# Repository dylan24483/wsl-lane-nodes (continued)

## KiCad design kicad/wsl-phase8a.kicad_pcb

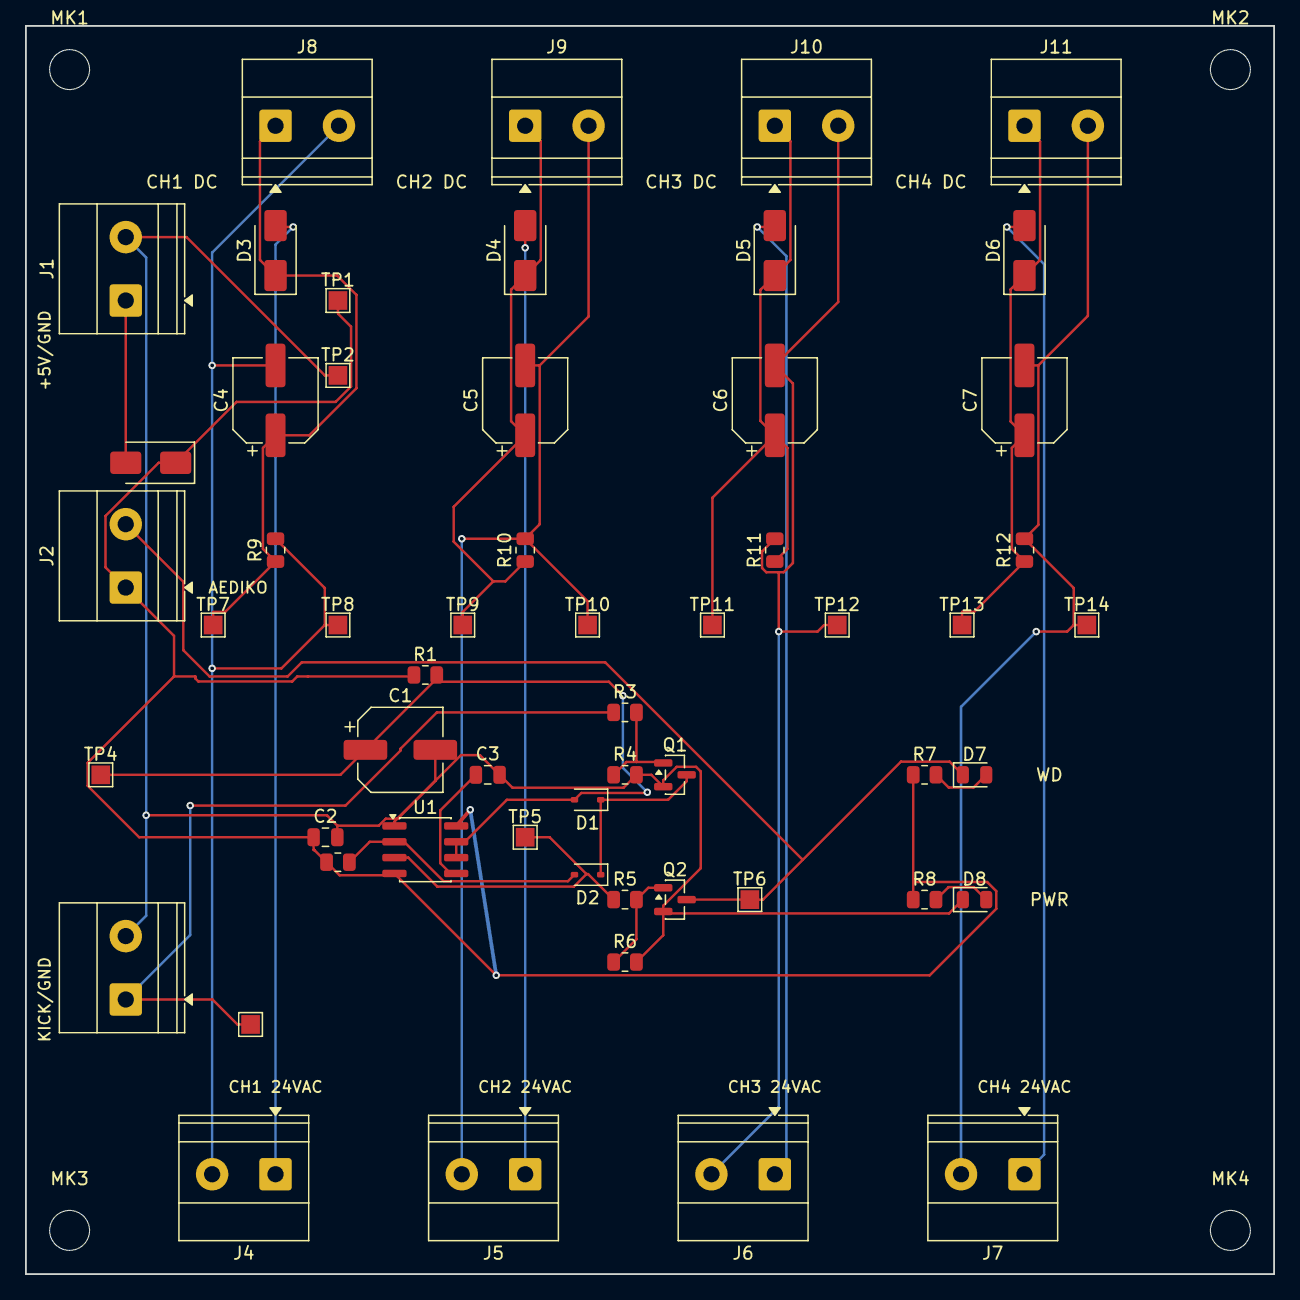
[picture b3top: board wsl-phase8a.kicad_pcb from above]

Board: 2 copper layers, 100.0 x 100.0 mm, 60 parts (0 on the bottom side), 26 nets.

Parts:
C1: 100uF/16V; CP_Elec_6.3x5.4
C2: 0.1uF/50V; C_0805_2012Metric
C3: 10nF/50V; C_0805_2012Metric
C4, C5, C6, C7: 10uF/63V; CP_Elec_6.3x5.4
D1, D2: 1N4148WS; D_SOD-323
D3, D4, D5, D6: M7 (1N4007); D_SMA
D7, D8: Green; LED_0805_2012Metric
D9: SS14; D_SMA
J1, J2, J3, J4, J5, J6, J7, J8, J9, J10, J11: 5.08mm 2P TB; TerminalBlock_Phoenix_MKDS-1,5-2-5.08_1x02_P5.08mm_Horizont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
MK1, MK2, MK3, MK4: MountingHole_3.2mm_M3
Q1, Q2: AO3400A; SOT-23
R1, R9, R10, R11, R12: 100k; R_0805_2012Metric
R2, R4, R6: 10k; R_0805_2012Metric
R3, R5: 1k; R_0805_2012Metric
R7, R8: 470; R_0805_2012Metric
TP1: VCC_5V; TestPoint_Pad_1.5x1.5mm
TP2: GND; TestPoint_Pad_1.5x1.5mm
TP3: KICK; TestPoint_Pad_1.5x1.5mm
TP4: TIMING_NODE; TestPoint_Pad_1.5x1.5mm
TP5: NE555_OUT; TestPoint_Pad_1.5x1.5mm
TP6: COIL_GND_RETURN; TestPoint_Pad_1.5x1.5mm
TP7: DC_CH1_POS; TestPoint_Pad_1.5x1.5mm
TP8: CH1_RETURN; TestPoint_Pad_1.5x1.5mm
TP9: DC_CH2_POS; TestPoint_Pad_1.5x1.5mm
TP10: CH2_RETURN; TestPoint_Pad_1.5x1.5mm
TP11: DC_CH3_POS; TestPoint_Pad_1.5x1.5mm
TP12: CH3_RETURN; TestPoint_Pad_1.5x1.5mm
TP13: DC_CH4_POS; TestPoint_Pad_1.5x1.5mm
TP14: CH4_RETURN; TestPoint_Pad_1.5x1.5mm
U1: NE555; SOIC-8_3.9x4.9mm_P1.27mm

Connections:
AC_CH1_L1: D3.2, J4.1
AC_CH2_L1: D4.2, J5.1
AC_CH3_L1: D5.2, J6.1
AC_CH4_L1: D6.2, J7.1
CH1_RETURN: C4.2, J4.2, J8.2, R9.2, TP8.1
CH2_RETURN: C5.2, J5.2, J9.2, R10.2, TP10.1
CH3_RETURN: C6.2, J6.2, J10.2, R11.2, TP12.1
CH4_RETURN: C7.2, J7.2, J11.2, R12.2, TP14.1
COIL_GND_RETURN: D7.1, J2.2, Q2.3, TP6.1
DC_CH1_POS: C4.1, D3.1, J8.1, R9.1, TP7.1
DC_CH2_POS: C5.1, D4.1, J9.1, R10.1, TP9.1
DC_CH3_POS: C6.1, D5.1, J10.1, R11.1, TP11.1
DC_CH4_POS: C7.1, D6.1, J11.1, R12.1, TP13.1
GND: C1.2, C2.2, C3.2, D8.1, J1.2, J3.2, Q1.2, Q2.2, R4.2, R6.2, TP2.1, U1.1
KICK: J3.1, R3.1, TP3.1
LED1_ANODE_DRIVE: D7.2, R7.2
LED2_ANODE_DRIVE: D8.2, R8.2
NE555_CTRL: C3.1, U1.5
NE555_OUT: R5.1, TP5.1, U1.3
NE555_TRIG: D2.2, R2.2, U1.2
Q1_DRAIN: D1.1, D2.1, Q1.3
Q1_GATE: Q1.1, R3.2, R4.1
Q2_GATE: Q2.1, R5.2, R6.1
TIMING_NODE: C1.1, D1.2, R1.2, TP4.1, U1.6, U1.7
VCC_5V: C2.1, D9.1, J2.1, R1.1, R2.1, R7.1, R8.1, TP1.1, U1.4, U1.8
VCC_5V_RAW: D9.2, J1.1

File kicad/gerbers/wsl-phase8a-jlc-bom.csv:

"Comment","Designator","Footprint","LCSC Part #"
"100uF/16V","C1","CP_Elec_6.3x5.4","C970684"
"0.1uF/50V","C2","C_0805_2012Metric","C49678"
"10nF/50V","C3","C_0805_2012Metric","C53084521"
"10uF/63V","C4,C5,C6,C7","CP_Elec_6.3x5.4","C2935114"
"1N4148WS","D1,D2","D_SOD-323","C917117"
"M7 (1N4007)","D3,D4,D5,D6","D_SMA","C95872"
"Green","D7,D8","LED_0805_2012Metric","C84260"
"SS14","D9","D_SMA","C2480"
"AO3400A","Q1,Q2","SOT-23","C20917"
"100k","R1,R9,R10,R11,R12","R_0805_2012Metric","C149504"
"10k","R2,R4,R6","R_0805_2012Metric","C2930231"
"1k","R3,R5","R_0805_2012Metric","C2907295"
"470","R7,R8","R_0805_2012Metric","C2907329"
"NE555","U1","SOIC-8_3.9x4.9mm_P1.27mm","C7593"

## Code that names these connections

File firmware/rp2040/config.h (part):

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
/* ---- UART (uart0) link to the Pi -------------------------------------------------------- */
#define UART_BAUD     115200
#define PIN_UART_TX   0   /* GP0, Pico pin 1  -> Pi RX   (net PI_UART_RX) */
#define PIN_UART_RX   1   /* GP1, Pico pin 2  <- Pi TX   (net PI_UART_TX) */

/* ---- Rail permission output ------------------------------------------------------------- */
#define PIN_RP_OK     2   /* GP2, Pico pin 4  -> RP2040_OK; HIGH=permit motion, LOW=drop rail */

/* ---- Fast inputs (opto, ACTIVE-LOW: asserted = GPIO LOW) -------------------------------- */
#define PIN_SA        6   /* GP6,  Pico pin 9  : sweep cam  (270 run-through stop / 360 zero)  */
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 * registers each heartbeat tick and latch_fault()s (fail-safe: drops RP_OK) on any
 * drift. The host test (test/test_v12.c) fails the build if any code path ever puts
 * GP16-19 in an output direction or writes them.                                        */
#define PIN_TAP_555    16   /* GP16, Pico pin 21 : TAP_NE555_OUT   (INVERTED: raw 0 = 555 out HIGH) */
#define PIN_TAP_KICK   17   /* GP17, Pico pin 22 : TAP_WDOG_KICK   (INVERTED)                       */
#define PIN_TAP_ARM    18   /* GP18, Pico pin 24 : TAP_ARM_PERMIT  (INVERTED)                       */
#define PIN_TAP_RPOK   19   /* GP19, Pico pin 25 : TAP_RP2040_OK   (INVERTED; cross-checked vs GP2) */
#define PIN_ADC_VCC5   26   /* GP26/ADC0, Pico pin 31 : ADC_VCC5_SENSE = VCC_5V/2 (10k/10k divider) */
#define ADC_VCC5_INPUT  0   /* ADC mux input for GP26 */

/* ---- v1.2.2 REV_ID board-revision straps (Codex R2-6) ----------------------------------- */
/* AUTHORITATIVE SOURCE: generate_kicad_netlist_revD.py block_j16_protection_and_revid()
 * (committed 2026-07-21, dc56964). GP20 (Pico pin 26) = REV_ID0, 10k strap; GP21 (Pico
 * pin 27) = REV_ID1, 10k strap. ENCODING: REV_ID[1:0] = GP21<<1 | GP20.
 *   rev-D board: REV_ID0 strapped to VCC_3V3 (reads 1), REV_ID1 to GND (reads 0) = 0b01.
 *   0b00 = reserved/legacy; 0b10/0b11 = future revisions.
 * On a rev-B/rev-C board these pins are UNCONNECTED (float). Detection: read once under
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 * reads = floating = REV_ID_FLOATING (reported "unknown", NEVER assumed rev-D). After the
 * read, pulls are disabled (zero static strap current) and the pins join the pad-OE
 * locked input-contract set.                                                              */
#define PIN_REV_ID0      20   /* GP20, Pico pin 26 : REV_ID bit 0 (rev-D: 10k to VCC_3V3) */
#define PIN_REV_ID1      21   /* GP21, Pico pin 27 : REV_ID bit 1 (rev-D: 10k to GND)     */
#define REV_ID_REVD      0x1u /* the code THIS firmware expects on a rev-D board          */
#define REV_ID_FLOATING  0xFFu/* sentinel: pull-phase reads disagreed (no straps fitted)  */
#define REV_ID_SETTLE_US 50u  /* pull -> read settle (10k/50k node settles in ~us; ample) */
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
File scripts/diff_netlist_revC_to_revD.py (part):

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# docs/phase8_revD_change_spec.md items A/C/D/E/F:
ALLOWED_TOUCHED_NETS = {
    "FIELD_WET_V",    # A: bleed pair; C: 8 x Rin_AUXn
    "FIELD_GND",      # A: bleed pair; C: J15 pins 9-10
    "VCC_5V",         # D: divider top; R2-4: F_J16_5V polyfuse input
                      #   (J16 pin 1 moved behind it, 2026-07-21 round 2)
    "GND",            # C: 8 x opto emitter; D: divider bottom + cap;
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                      # R2-4: buffer GND + bypass + ESD VN/spare; R2-6: REV_ID1 strap
    "VCC_3V3",        # C: 8 x Rpu_AUXn; E(R1): 4 x R_TAPPU; R2-4: solder-link
                      #   input + buffer VCC/EN + card-side pull-ups + bypass
                      #   (J16 pin 5 moved behind the link); R2-6: REV_ID0 strap
    "I2C_SDA",        # R2-4: TCA4307 SDAIN (J16 pin 3 moved behind the buffer)
    "I2C_SCL",        # R2-4: TCA4307 SCLIN (J16 pin 4 moved behind the buffer)
    "NE555_OUT",      # E(R1): R_TAPIN_555 series input
    "WDOG_KICK",      # E(R1): R_TAPIN_KICK series input
    "ARM_PERMIT",     # E(R1): R_TAPIN_ARM series input
    "RP2040_OK",      # E(R1): R_TAPIN_RPOK series input
}

# --------------------------------------------------------------------------
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                  ("R_WET_BLEED1", "2"), ("R_WET_BLEED2", "2")},
    "FIELD_WET_V": ({("R_WET_BLEED1", "1"), ("R_WET_BLEED2", "1")}
                    | {(f"Rin_AUX{i}", "1") for i in range(4, 12)}),
    # R2-4 (2026-07-21): J16 pin 1 now lands on J16_5V (an ADDED net).
    # Round-3: ESD VP (D_ESD_J16.5) rides VCC_5V UPSTREAM of the polyfuse.
    "VCC_5V": {("F_J16_5V", "1"), ("R_ADC5_TOP", "1"), ("D_ESD_J16", "5")},
    "GND": ({("C_ADC5", "2"), ("J_EXTI2C", "2"), ("J_EXTI2C", "6"),
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                | {("JP_J16_3V3", "1"), ("U_I2C_BUF", "8"), ("U_I2C_BUF", "1"),
                   ("R_J16_SDA_PU", "1"), ("R_J16_SCL_PU", "1"),
                   ("C_I2C_BUF", "1"), ("R_REVID0", "1")}),
    "I2C_SDA": {("U_I2C_BUF", "6")},   # R2-4: SDAIN (J16 pin 3 now buffered)
    "I2C_SCL": {("U_I2C_BUF", "3")},   # R2-4: SCLIN (J16 pin 4 now buffered)
    "NE555_OUT": {("R_TAPIN_555", "1")},
    "WDOG_KICK": {("R_TAPIN_KICK", "1")},
    "ARM_PERMIT": {("R_TAPIN_ARM", "1")},
    "RP2040_OK": {("R_TAPIN_RPOK", "1")},
}
for _n in R6_REVC_CHANNELS:                                            # r6
    EXPECTED_TOUCHED_NET_ADDITIONS[f"FIELD_LED_{_n}"] = {
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
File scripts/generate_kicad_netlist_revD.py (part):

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  C - IN-B GPB opto bank: 8 exact opto_input() clones AUX4-AUX11 appended at
      the END of SLOW_INPUT_PINS -> MCP_IN_B (0x21) pins 1-8 (GPB0-7), plus
      new field connector J15 = J_SLOW_IN_C (Conn_01x10 on FP_MCV_1X10,
      pinout mirrors J3 keying: signals 1-8, FIELD_GND 9-10). Mating plug
      Phoenix MC 1,5/10-ST-3,5 = 1840447 (harness BOM) — SAME plug PN as J3
      on the same field edge: cross-mate hazard; CP-MSTB 1734634 coding keys
      at different positions are MANDATORY (spec §C.3, gate OG-3).
      25 parts, 24 new nets.
  D - VCC_5V board-self-health ADC divider: 10k/10k + 100nF -> new net
      ADC_VCC5_SENSE -> Pico pin 31 (GP26/ADC0). ADC_VREF (pin 35) stays NC
      (module-internal reference, spec drift DR-3). 3 parts, 1 new net.
  E - Rail-drop edge-ordering taps on EXISTING observable points only.
      2026-07-21 REDESIGN (remediation spec R1, closes Codex C1 + H1 —
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INT_B = Net("MCP_INT_B")
RAIL_EN = Net("RELAY_ENABLE_RAIL")
# Rev-D round-2 (Codex R2-4): J16 no longer touches the raw rails/bus.
# Pin 1 sits behind a 200 mA polyfuse (J16_5V), pin 5 behind a default-OPEN
# solder link (J16_3V3), pins 3/4 behind a TCA4307 stuck-bus-recovery I2C
# buffer (J16_SDA/J16_SCL). All four are LOGIC-domain nets.
J16_5V = Net("J16_5V")
J16_3V3 = Net("J16_3V3")
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    led_series = Net(f"FIELD_LED_{name}")

    # Dry-contact default: WET -> Rin -> Dser -> opto LED -> field pin. The
    # field contact closes that pin to FIELD_GND at the connector/harness.
    WET += rin[1]
    rin_series += rin[2]
    led_series += opto[1]
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    FGND += j_slowb[12]

    # Rev-D item C: J15 pinout mirrors J3's keying pattern (signals 1-8,
    # doubled FIELD_GND on the last two pins).
    slowc_order = [f"AUX{i}" for i in range(4, 12)]
    for pin, name in enumerate(slowc_order, start=1):
        slow_field[name] += j_slowc[pin]
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    # Rev-D item F, REVISED by round-2 remediation R2-4 (2026-07-21): the
    # J16 pin functions are unchanged (5V / GND / SDA / SCL / 3V3 / GND) but
    # every non-GND pin now lands on a PROTECTED net:
    #   pin 1 -> J16_5V   (behind the F_J16_5V 200 mA polyfuse)
    #   pin 3 -> J16_SDA  (behind the TCA4307 buffer + local pull-up + ESD)
    #   pin 4 -> J16_SCL  (ditto)
    #   pin 5 -> J16_3V3  (behind the JP_J16_3V3 default-OPEN solder link —
    #                      the pin ships NC; bridge only for a verified
    #                      3.3 V module)
    # A wedged/shorted external module can no longer wedge the main I2C bus
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    polyfuse are NOT isolation-barrier parts — every pin lands on LOGIC
    nets; the PC817/G5LE barrier inventory is untouched):
      * F_J16_5V  — Littelfuse 1206L020YR polyfuse (200 mA hold / 420 mA
        trip / 24 V @ 23 C), VCC_5V -> J16_5V -> J16 pin 1. Protects the
        module branch; PPTC trip current is time/temperature dependent, not
        a hard current clamp. The
        sanctioned steady module allowance is 45 mA (R3-7, re-derived from
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        the polyfuse (round-3 fix — VP on the fused J16_5V node let a
        bridged-JP1 board defeat the fuse through IO1's upper steering
        diode on a J16 5V-to-GND short), steering IOs on J16_SDA (3),
        J16_SCL (6), J16_3V3 (1), and J16_5V (4) so the fused 5 V pin
        keeps its ESD clamp.

    REV_ID straps (Codex R2-6): 2-bit board-revision code on spare Pico
    GPIOs, read by firmware (v1.2.2 task) and reported in the identity
    line so the daemon can reject roles unsupported by the physical board.
      * GP20 (pin 26) = REV_ID0 — 10k strap to VCC_3V3 (reads 1)
      * GP21 (pin 27) = REV_ID1 — 10k strap to GND     (reads 0)
    ENCODING (REV_ID[1:0] = GP21<<1 | GP20):
      0b00 = reserved/legacy (no straps — a rev-C-class board would float;
             firmware must treat unreadable/floating as UNKNOWN, not rev-D)
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    #     J16_5V node permanently). Now: VP rides VCC_5V UPSTREAM of the
    #     polyfuse (a solid rail — steering diodes from any shorted IO pin
    #     are reverse-biased, clamp energy still lands on a decoupled rail)
    #     and the fused J16_5V pin gets the previously-spare IO3 channel so
    #     the connector's 5 V pin keeps ESD protection. Under the same
    #     fault: IO3 lower diode to VN reverse-biased, IO3 upper diode
    #     (0 V -> 5 V VP) reverse-biased — NO sneak path, fuse does its job. ---
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    J16_3V3 += esd[1]            # IO1
    GND += esd[2]                # VN
    J16_SDA += esd[3]            # IO2
    J16_5V += esd[4]             # IO3 — fused 5V pin as an IO channel (round-3)
    VCC5 += esd[5]               # VP — UPSTREAM of the polyfuse (round-3)
    J16_SCL += esd[6]            # IO4

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    r_id1 = add_res("R_REVID1", "10k")
    rev0 = Net("REV_ID0")
    rev1 = Net("REV_ID1")
    VCC3V3 += r_id0[1]           # rev-D: REV_ID0 = 1
    rev0 += r_id0[2], pico[26]   # GP20
    GND += r_id1[1]              # rev-D: REV_ID1 = 0
    rev1 += r_id1[2], pico[27]   # GP21


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
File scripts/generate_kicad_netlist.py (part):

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  LED1, LED2     LED1, LED2    Watchdog-healthy + power-good indicators
  TB_PWR_IN      J1            +5V power input
  TB_AEDIKO_PWR  J2            5V out to AEDIKO PWR (V+ direct, V- gated by Q2)
  TB_KICK        J3            Pi GPIO 12 watchdog kick input
  TB_AC_IN_CH*   J4..J7        24VAC channel inputs (foul/2nd-ball lamps)
  TB_DC_OUT_CH*  J8..J11       DC channel outputs to AL-ZARD selector inputs

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GND += LED2['K']  # LED2 cathode (power-good LED, cathode to GND)
GND += J3[2]      # TB_KICK.2 (kick GND reference, back to Pi)

# --- KICK (Pi GPIO 12 input to watchdog) ---
KICK += J3[1]     # TB_KICK.1
KICK += R3[1]     # Q1 gate series, top

# --- Q1_GATE (gate-drive network) ---
Q1_GATE += R3[2]  # Q1 gate series, bottom
Q1_GATE += R4[1]  # Q1 gate pulldown, top
Q1_GATE += Q1[1]  # Q1 gate (SOT-23 pin 1 = G)

# --- Q1_DRAIN (diode-OR isolation node) ---
Q1_DRAIN += Q1[3]    # Q1 drain (SOT-23 pin 3 = D)
Q1_DRAIN += D1['K']  # D1 cathode (Q1 pulls this LOW when ON)
Q1_DRAIN += D2['K']  # D2 cathode

# --- TIMING_NODE (NE555 RC + diode-OR anode for TIMING) ---
TIMING_NODE += U1[6]    # THRES (NE555 pin 6)
TIMING_NODE += U1[7]    # DISCH (NE555 pin 7)
TIMING_NODE += R1[2]    # Timing pullup, bottom
TIMING_NODE += C1[1]  # Timing cap +
TIMING_NODE += D1['A']  # D1 anode — when Q1 ON, D1 pulls TIMING_NODE down
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
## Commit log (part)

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2026-05-02 Initial commit: night-1 Phase 8 prototype with real wsl_scoring_engine
2026-05-02 Add server-initiated commands (OPEN/CLOSE/RESET) + desk simulator UI
    - Pi handles new command types with distinct LED patterns
    - Server exposes POST /api/lane/{N}/{open,close,reset}
    - HTML adds 3 buttons that POST these commands
    - OPEN_LANE also resets the LaneScoring state (new bowlers, fresh score)
    - Bridges sync HTTP handler to async websocket via run_coroutine_threadsafe
2026-05-13 Add 100kΩ bleeders Rb1..Rb4 across each AC interposer output
    Defensive against disconnected-AL-ZARD / future-module-swap scenarios;
    makes cap discharge deterministic when downstream load goes away.
    Per Codex review 2026-05-13. No physical re-test required — passive
    high-value resistor in parallel with cap, well-understood electrical
    behavior. 6.25mW per channel, τ=1s, same LCSC part as R1 timing.
2026-05-31 docs(phase8): add session handoff + lock in Phase 8 docs and FSM
